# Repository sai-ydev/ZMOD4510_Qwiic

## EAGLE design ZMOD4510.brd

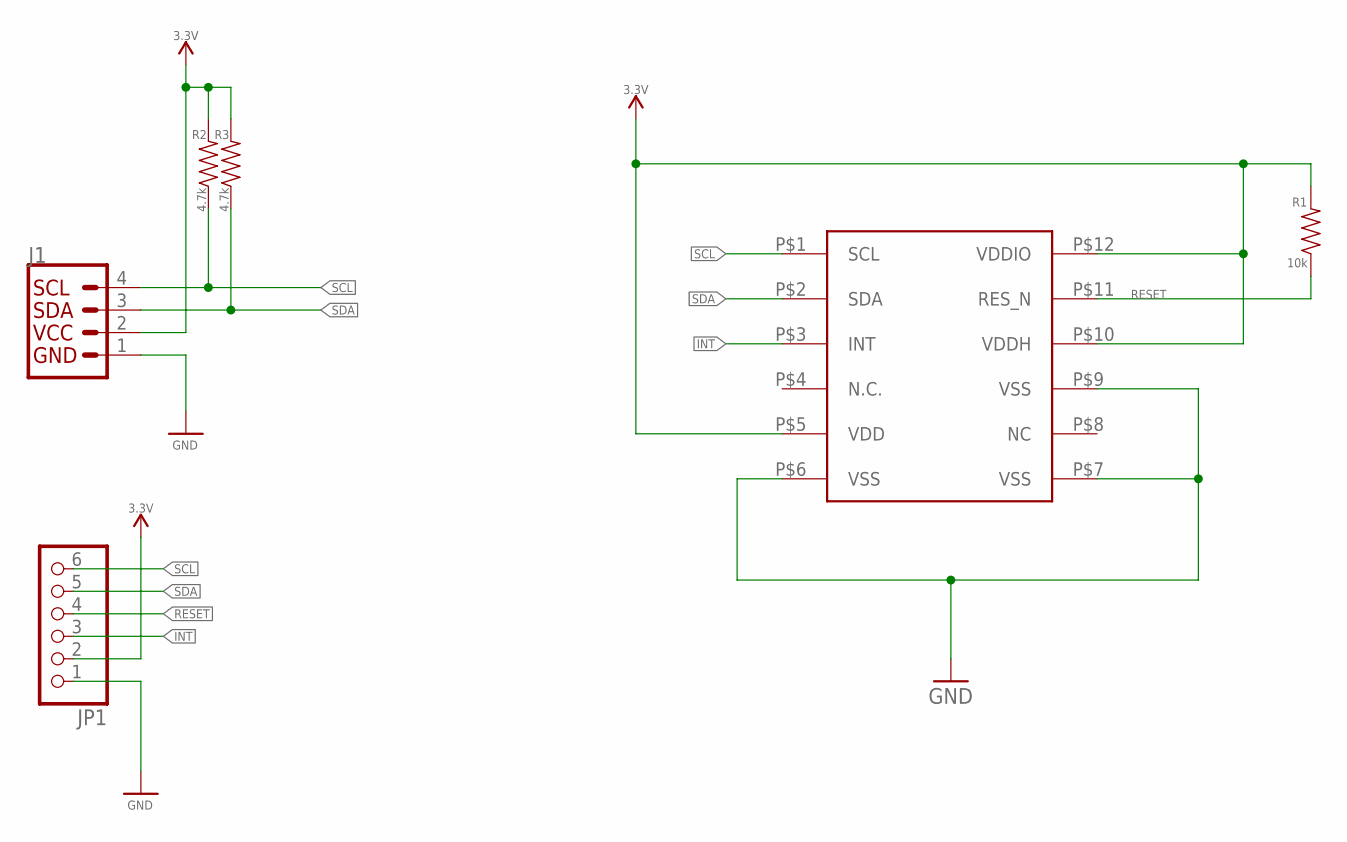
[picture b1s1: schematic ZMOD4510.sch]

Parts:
J1: QWIIC_CONNECTORJS-1MM; 1X04_1MM_RA
JP1: PINHD-1X6; 1X06
R1: 10k; 0603
R2, R3: 4.7k; 0603
U1: ZMOD4510

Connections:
3.3V: J1.2, JP1.2, R1.2, R2.2, R3.2, U1.P$5 (VDD), U1.P$10 (VDDH), U1.P$12 (VDDIO)
GND: J1.1, JP1.1, U1.P$6 (VSS), U1.P$7 (VSS), U1.P$9 (VSS)
INT: JP1.3, U1.P$3 (INT)
RESET: JP1.4, R1.1, U1.P$11 (RES_N)
SCL: J1.4, JP1.6, R2.1, U1.P$1 (SCL)
SDA: J1.3, JP1.5, R3.1, U1.P$2 (SDA)

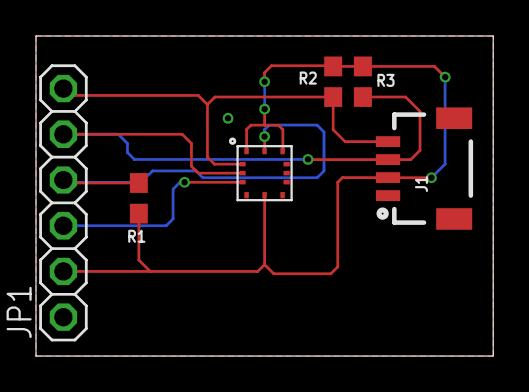
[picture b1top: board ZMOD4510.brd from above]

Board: 2 copper layers, 25.4 x 17.8 mm, 6 parts (0 on the bottom side), 6 nets.

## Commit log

2019-11-01 ZMod files

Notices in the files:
parts and their libraries:
SparkFun-Connectors: Licensing: Creative Commons ShareAlike 4.0 International - https://creativecommons.org/licenses/by-sa/4.0
